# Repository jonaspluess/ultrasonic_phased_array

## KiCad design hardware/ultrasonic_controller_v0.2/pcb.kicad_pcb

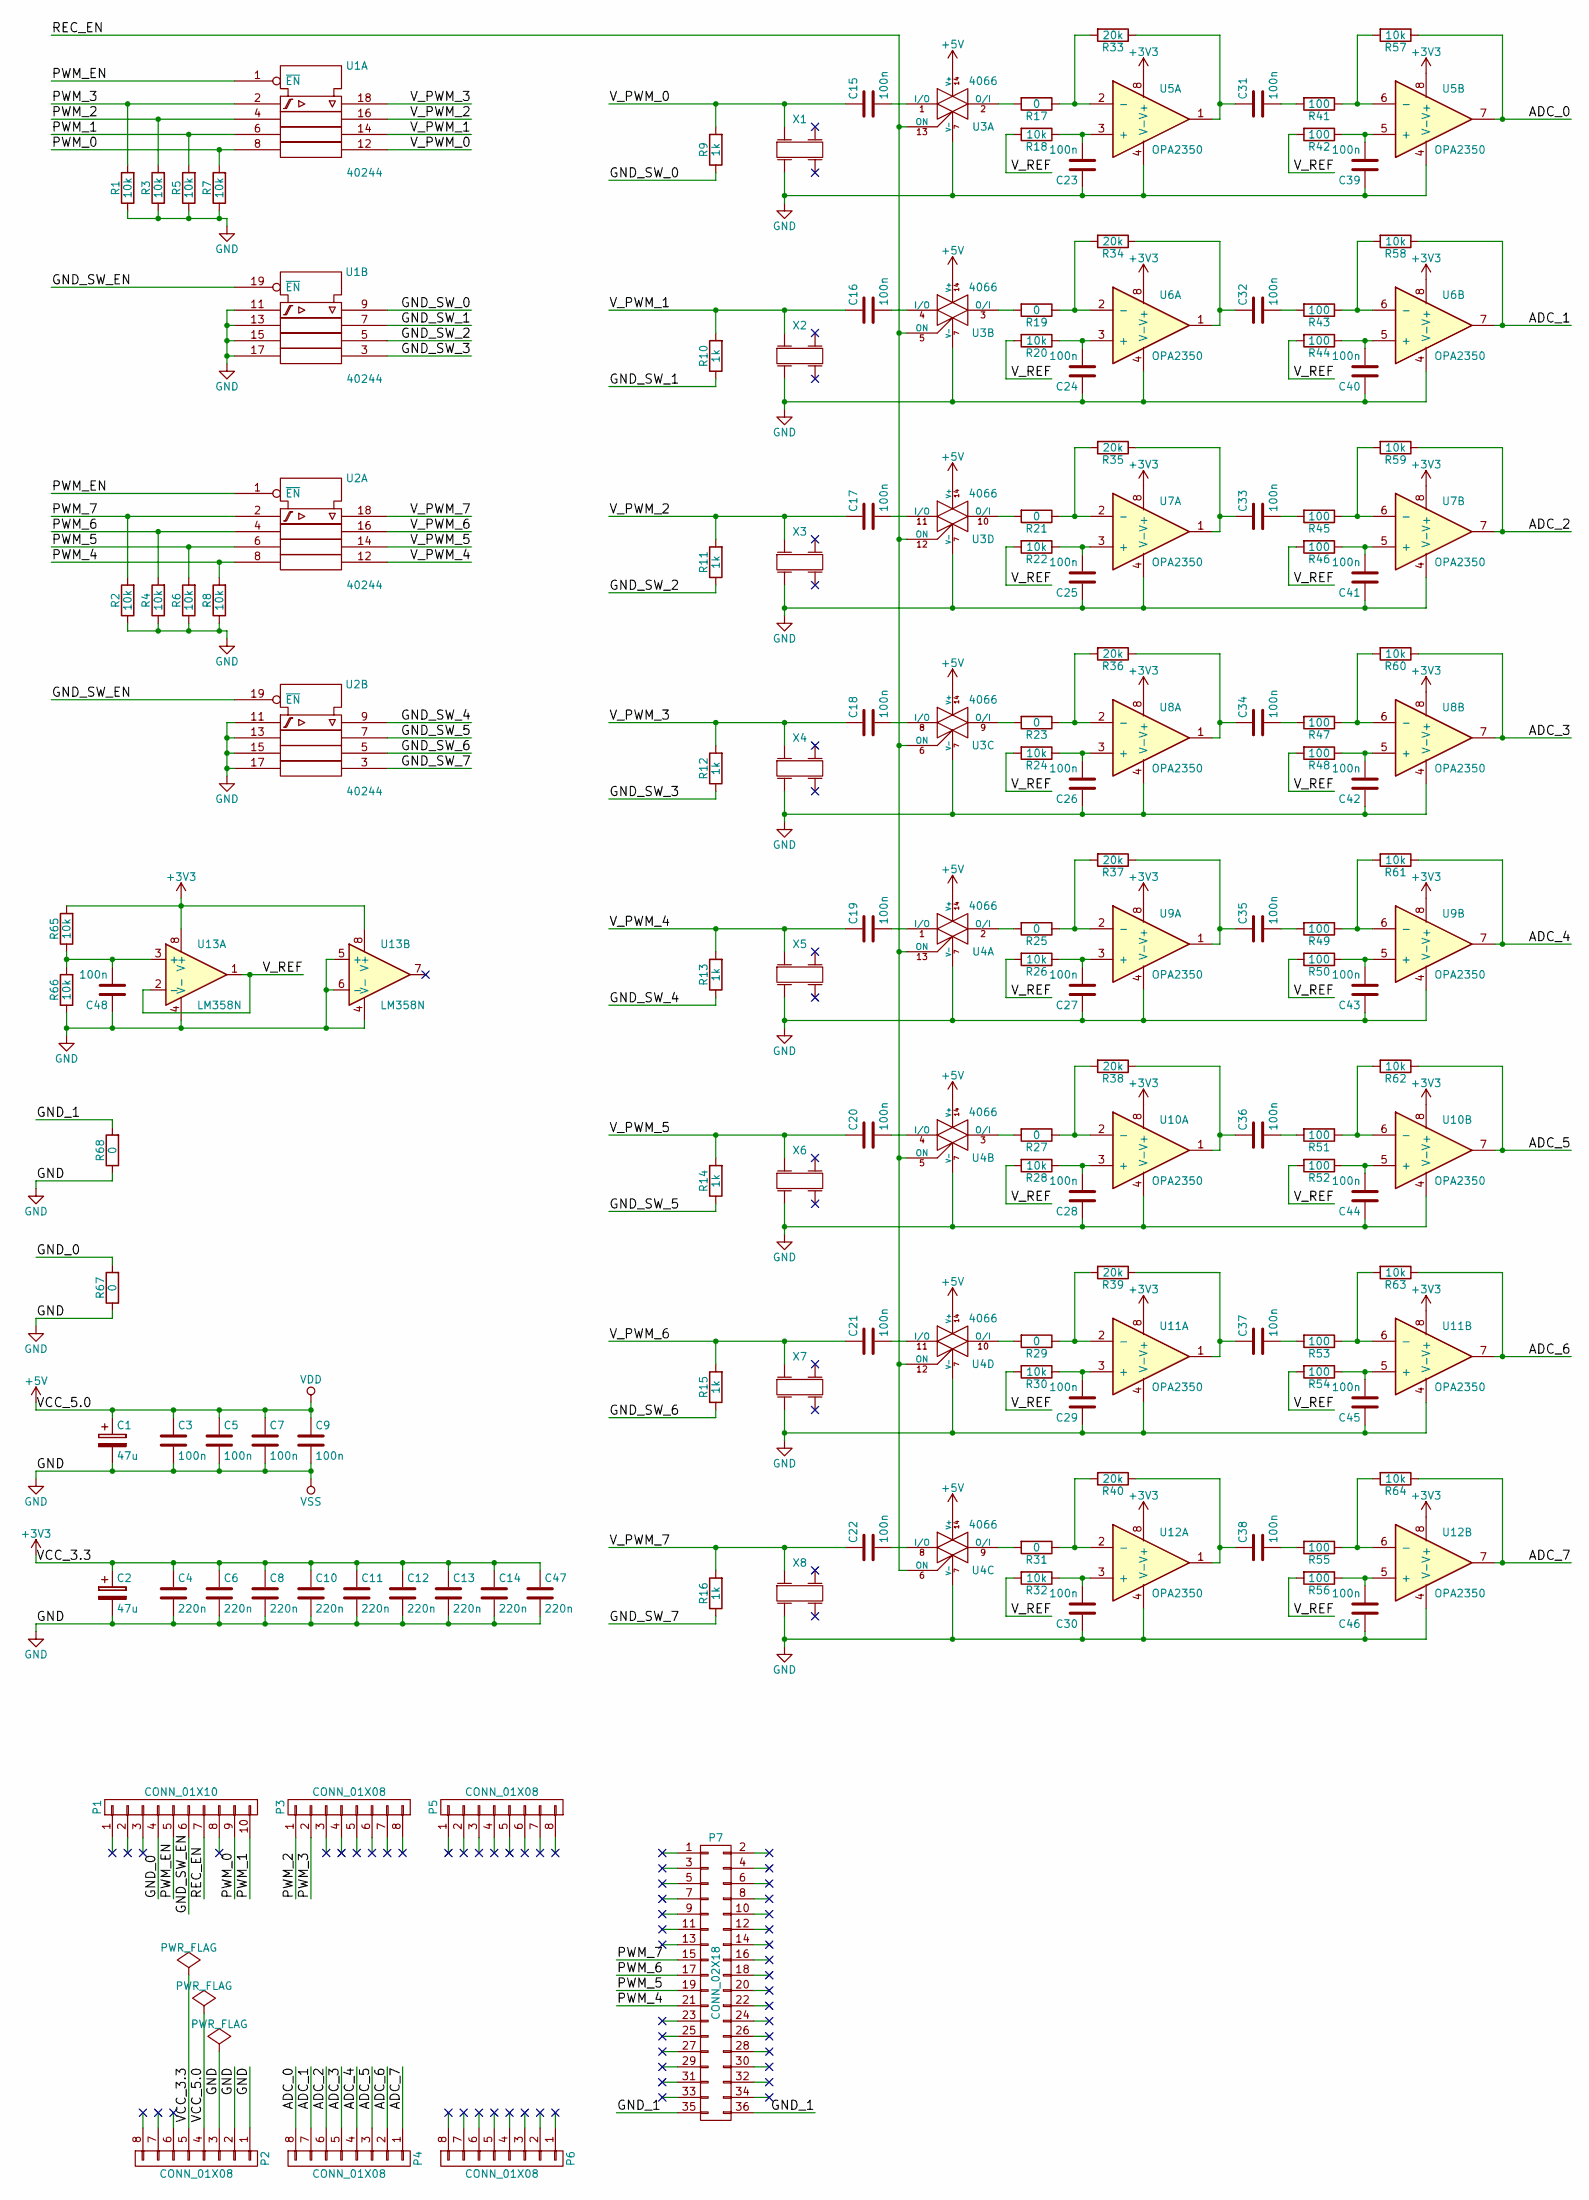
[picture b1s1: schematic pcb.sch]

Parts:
C1, C2: 47u; c_elec_6.3x5.8
C3, C5, C7, C9, C15, C16, C17, C18, C19, C20, C21, C22, C23, C24, C25, C26, C27, C28, C29, C30, C31, C32, C33, C34, C35, C36, C37, C38, C39, C40, C41, C42, C43, C44, C45, C46, C48: 100n; C_0805
C4, C6, C8, C10, C11, C12, C13, C14, C47: 220n; C_0805
P1: CONN_01X10; Pin_Header_Straight_1x10
P2, P3, P4, P5, P6: CONN_01X08; Pin_Header_Straight_1x08
P7: CONN_02X18; Pin_Header_Straight_2x18
R1, R2, R3, R4, R5, R6, R7, R8, R18, R20, R22, R24, R26, R28, R30, R32, R57, R58, R59, R60, R61, R62, R63, R64, R65, R66: 10k; R_0805
R9, R10, R11, R12, R13, R14, R15, R16: 1k; R_0805
R17, R19, R21, R23, R25, R27, R29, R31, R67, R68: 0; R_0805
R33, R34, R35, R36, R37, R38, R39, R40: 20k; R_0805
R41, R42, R43, R44, R45, R46, R47, R48, R49, R50, R51, R52, R53, R54, R55, R56: 100; R_0805
U1, U2: 40244; SOIC-20W_7.5x12.8mm_Pitch1.27mm
U3, U4: 4066; SOIC-14_N
U5, U6, U7, U8, U9, U10, U11, U12: OPA2350; SOIC-8_3.9x4.9mm_Pitch1.27mm
U13: LM358N; SOIC-8_3.9x4.9mm_Pitch1.27mm
X1, X2, X3, X4, X5, X6, X7, X8: PiezoelectricCrystal-TwoPairsOfelectrodes_EN60617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; murata_ultrasonic_transducer

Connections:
+3V3: C2.1, C4.1, C6.1, C8.1, C10.1, C11.1, C12.1, C13.1, C14.1, C47.1, P2.5, R65.2, U5.8 (V+), U6.8 (V+), U7.8 (V+), U8.8 (V+), U9.8 (V+), U10.8 (V+), U11.8 (V+), U12.8 (V+), U13.8 (V+)
+5V: C1.1, C3.1, C5.1, C7.1, C9.1, P2.4, U1.20 (Vdd), U2.20 (Vdd), U3.14 (V+), U4.14 (V+)
/ADC_0: P4.8, R57.1, U5.7
/ADC_1: P4.7, R58.1, U6.7
/ADC_2: P4.6, R59.1, U7.7
/ADC_3: P4.5, R60.1, U8.7
/ADC_4: P4.4, R61.1, U9.7
/ADC_5: P4.3, R62.1, U10.7
/ADC_6: P4.2, R63.1, U11.7
/ADC_7: P4.1, R64.1, U12.7
/GND_0: P1.4, R67.2
/GND_1: P7.35, P7.36, R68.2
/GND_SW_0: R9.1, U1.9
/GND_SW_1: R10.1, U1.7
/GND_SW_2: R11.1, U1.5
/GND_SW_3: R12.1, U1.3
/GND_SW_4: R13.1, U2.9
/GND_SW_5: R14.1, U2.7
/GND_SW_6: R15.1, U2.5
/GND_SW_7: R16.1, U2.3
/GND_SW_EN: P1.6, U1.19 (~EN), U2.19 (~EN)
/PWM_0: P1.9, R7.2, U1.8
/PWM_1: P1.10, R5.2, U1.6
/PWM_2: P3.1, R3.2, U1.4
/PWM_3: P3.2, R1.2, U1.2
/PWM_4: P7.21, R8.2, U2.8
/PWM_5: P7.19, R6.2, U2.6
/PWM_6: P7.17, R4.2, U2.4
/PWM_7: P7.15, R2.2, U2.2
/PWM_EN: P1.5, U1.1 (~EN), U2.1 (~EN)
/REC_EN: P1.7, U3.5 (ON), U3.6 (ON), U3.12 (ON), U3.13 (ON), U4.5 (ON), U4.6 (ON), U4.12 (ON), U4.13 (ON)
/V_PWM_0: C15.1, R9.2, U1.12, X1.1
/V_PWM_1: C16.1, R10.2, U1.14, X2.1
/V_PWM_2: C17.1, R11.2, U1.16, X3.1
/V_PWM_3: C18.1, R12.2, U1.18, X4.1
/V_PWM_4: C19.1, R13.2, U2.12, X5.1
/V_PWM_5: C20.1, R14.2, U2.14, X6.1
/V_PWM_6: C21.1, R15.2, U2.16, X7.1
/V_PWM_7: C22.1, R16.2, U2.18, X8.1
/V_REF: R18.2, R20.2, R22.2, R24.2, R26.2, R28.2, R30.2, R32.2, R42.2, R44.2, R46.2, R48.2, R50.2, R52.2, R54.2, R56.2, U13.1, U13.2 (-)
GND: C1.2, C2.2, C3.2, C4.2, C5.2, C6.2, C7.2, C8.2, C9.2, C10.2, C11.2, C12.2, C13.2, C14.2, C23.1, C24.1, C25.1, C26.1, C27.1, C28.1, C29.1, C30.1, C39.1, C40.1, C41.1, C42.1, C43.1, C44.1, C45.1, C46.1, C47.2, C48.1, P2.1, P2.2, P2.3, R1.1, R2.1, R3.1, R4.1, R5.1, R6.1, R7.1, R8.1, R66.1, R67.1, R68.1, U1.10 (Vss), U1.11, U1.13, U1.15, U1.17, U2.10 (Vss), U2.11, U2.13, U2.15, U2.17, U3.7 (V-), U4.7 (V-), U5.4 (V-), U6.4 (V-), U7.4 (V-), U8.4 (V-), U9.4 (V-), U10.4 (V-), U11.4 (V-), U12.4 (V-), U13.4 (V-), U13.5 (+), U13.6 (-), X1.3, X2.3, X3.3, X4.3, X5.3, X6.3, X7.3, X8.3
unnamed: C15.2, U3.1 (I/O)
unnamed: C16.2, U3.4 (I/O)
unnamed: C17.2, U3.11 (I/O)
unnamed: C18.2, U3.8 (I/O)
unnamed: C19.2, U4.1 (I/O)
unnamed: C20.2, U4.4 (I/O)
unnamed: C21.2, U4.11 (I/O)
unnamed: C22.2, U4.8 (I/O)
unnamed: C23.2, R18.1, U5.3 (+)
unnamed: C24.2, R20.1, U6.3 (+)
unnamed: C25.2, R22.1, U7.3 (+)
unnamed: C26.2, R24.1, U8.3 (+)
unnamed: C27.2, R26.1, U9.3 (+)
unnamed: C28.2, R28.1, U10.3 (+)
unnamed: C29.2, R30.1, U11.3 (+)
unnamed: C30.2, R32.1, U12.3 (+)
unnamed: C31.1, R33.1, U5.1
unnamed: C31.2, R41.2
unnamed: C32.1, R34.1, U6.1
unnamed: C32.2, R43.2
unnamed: C33.1, R35.1, U7.1
unnamed: C33.2, R45.2
unnamed: C34.1, R36.1, U8.1
unnamed: C34.2, R47.2
unnamed: C35.1, R37.1, U9.1
unnamed: C35.2, R49.2
unnamed: C36.1, R38.1, U10.1
unnamed: C36.2, R51.2
unnamed: C37.1, R39.1, U11.1
unnamed: C37.2, R53.2
unnamed: C38.1, R40.1, U12.1
unnamed: C38.2, R55.2
unnamed: C39.2, R42.1, U5.5 (+)
unnamed: C40.2, R44.1, U6.5 (+)
unnamed: C41.2, R46.1, U7.5 (+)
unnamed: C42.2, R48.1, U8.5 (+)
unnamed: C43.2, R50.1, U9.5 (+)
unnamed: C44.2, R52.1, U10.5 (+)
unnamed: C45.2, R54.1, U11.5 (+)
unnamed: C46.2, R56.1, U12.5 (+)
unnamed: C48.2, R65.1, R66.2, U13.3 (+)
unnamed: R17.1, R33.2, U5.2 (-)
unnamed: R17.2, U3.2 (O/I)
unnamed: R19.1, R34.2, U6.2 (-)
unnamed: R19.2, U3.3 (O/I)
unnamed: R21.1, R35.2, U7.2 (-)
unnamed: R21.2, U3.10 (O/I)
unnamed: R23.1, R36.2, U8.2 (-)
unnamed: R23.2, U3.9 (O/I)
unnamed: R25.1, R37.2, U9.2 (-)
unnamed: R25.2, U4.2 (O/I)
unnamed: R27.1, R38.2, U10.2 (-)
unnamed: R27.2, U4.3 (O/I)
unnamed: R29.1, R39.2, U11.2 (-)
unnamed: R29.2, U4.10 (O/I)
unnamed: R31.1, R40.2, U12.2 (-)
unnamed: R31.2, U4.9 (O/I)
unnamed: R41.1, R57.2, U5.6 (-)
unnamed: R43.1, R58.2, U6.6 (-)
unnamed: R45.1, R59.2, U7.6 (-)
unnamed: R47.1, R60.2, U8.6 (-)
unnamed: R49.1, R61.2, U9.6 (-)
unnamed: R51.1, R62.2, U10.6 (-)
unnamed: R53.1, R63.2, U11.6 (-)
unnamed: R55.1, R64.2, U12.6 (-)

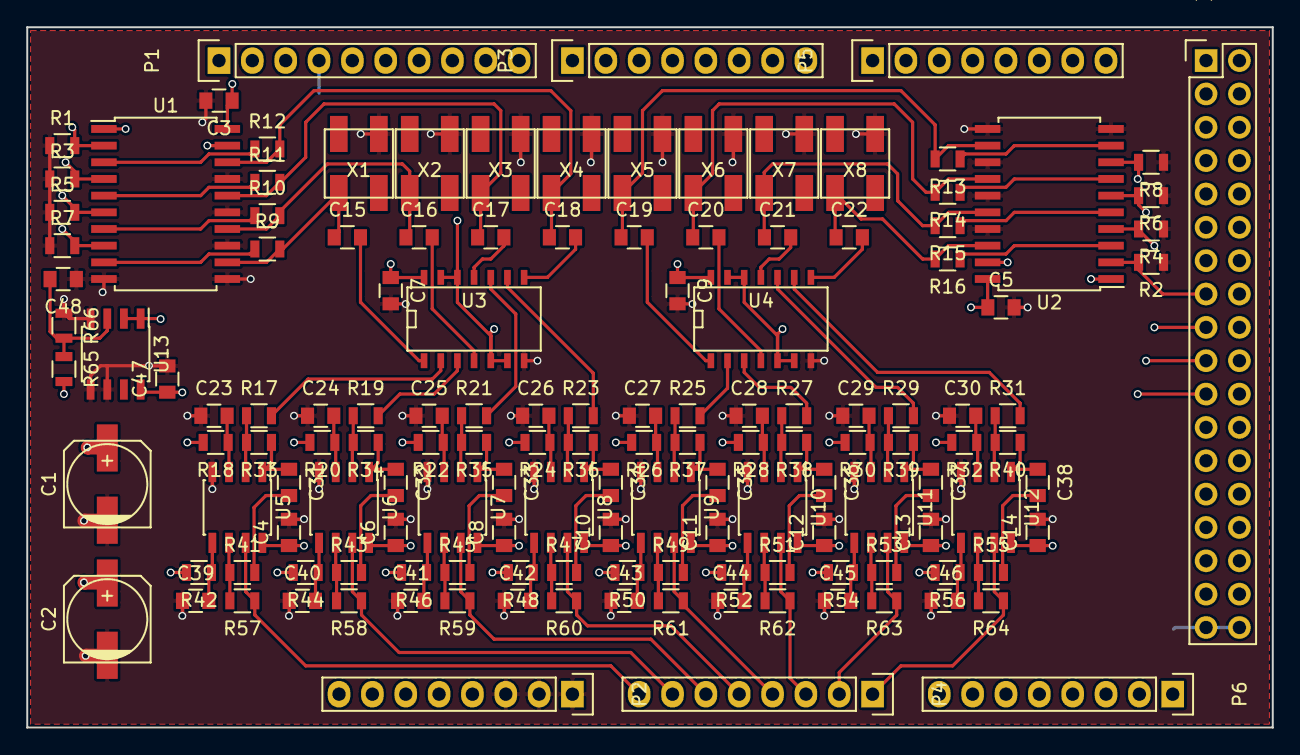
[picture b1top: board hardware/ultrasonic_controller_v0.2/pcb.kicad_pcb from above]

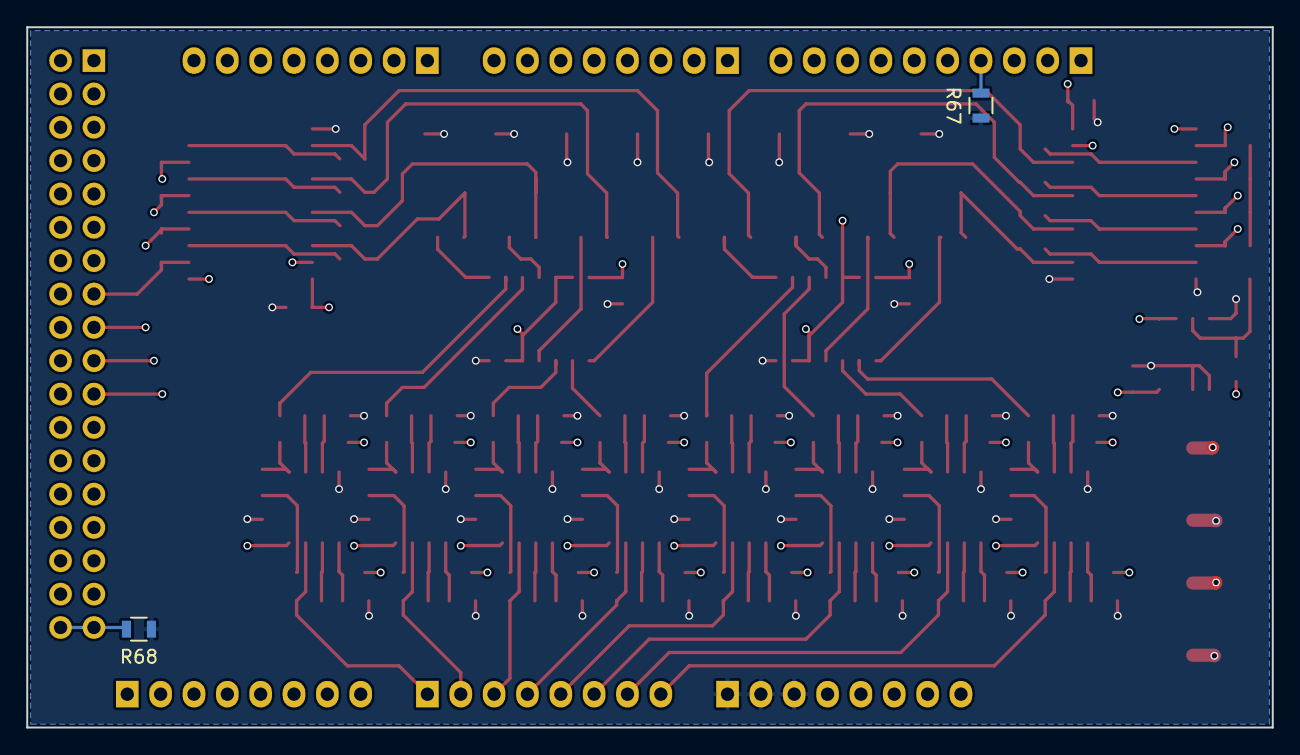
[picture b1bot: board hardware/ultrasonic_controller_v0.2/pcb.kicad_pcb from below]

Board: 4 copper layers, 94.9 x 53.3 mm, 144 parts (2 on the bottom side), 106 nets.

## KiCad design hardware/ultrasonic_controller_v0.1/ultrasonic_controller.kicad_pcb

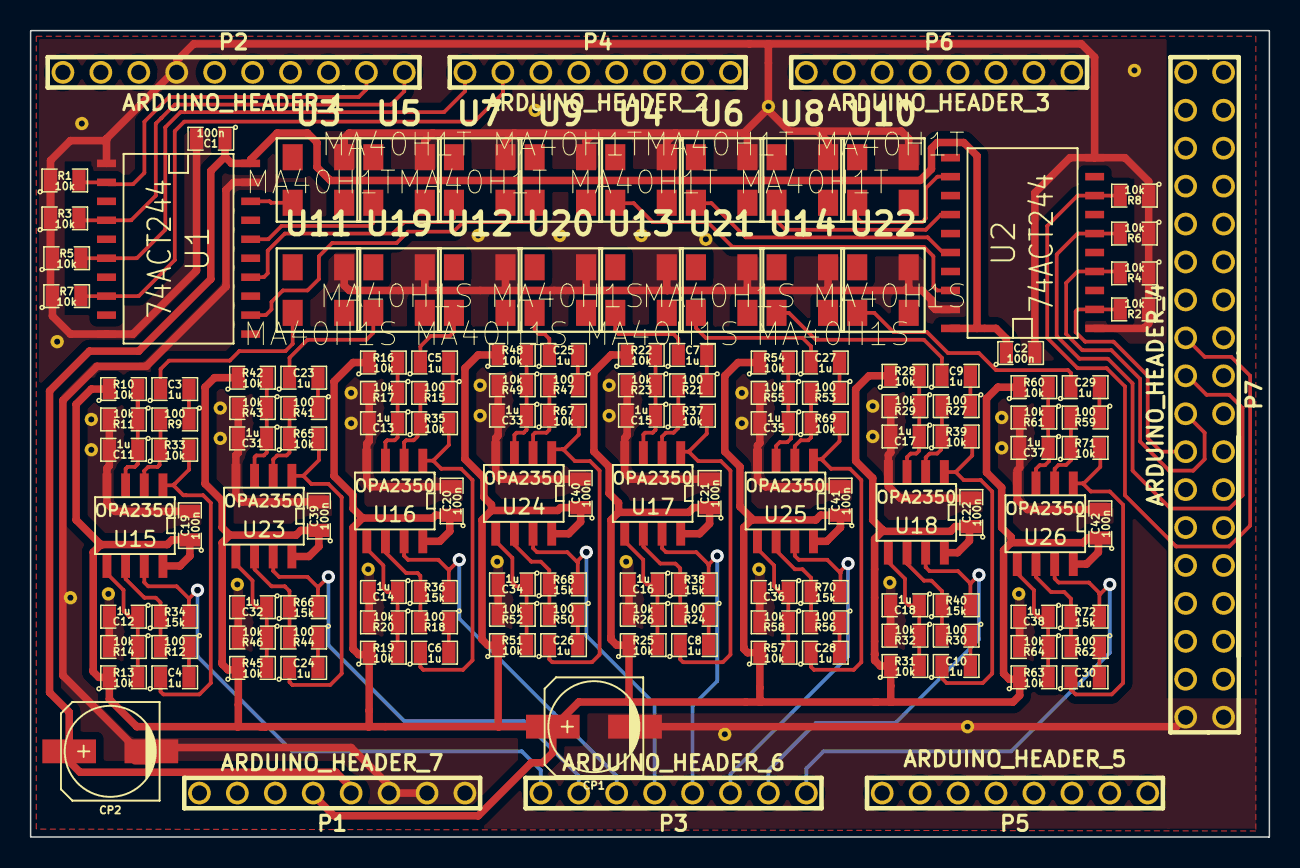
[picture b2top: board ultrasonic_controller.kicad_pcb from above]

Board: 2 copper layers, 82.9 x 54.0 mm, 188 parts (0 on the bottom side), 91 nets.

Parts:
C1, C2, C19, C20, C21, C22, C39, C40, C41, C42: 100n; SM0805
C3, C4, C5, C6, C7, C8, C9, C10, C11, C12, C13, C14, C15, C16, C17, C18, C23, C24, C25, C26, C27, C28, C29, C30, C31, C32, C33, C34, C35, C36, C37, C38: 1u; SM0805
CP1, CP2: 10u; c_elec_6.3x5.8
GroundVia: VAL**; GroundVia
GroundVia#2, GroundVia#3, GroundVia#4, GroundVia#5, GroundVia#6, GroundVia#7, GroundVia#8, GroundVia#9, GroundVia#10, GroundVia#11, GroundVia#12, GroundVia#13, GroundVia#14, GroundVia#15, GroundVia#16, GroundVia#17, GroundVia#18, GroundVia#19, GroundVia#20, GroundVia#21, GroundVia#22, GroundVia#23, GroundVia#24, GroundVia#25, GroundVia#26, GroundVia#27, GroundVia#28, GroundVia#29, GroundVia#30, GroundVia#31, GroundVia#32, GroundVia#33, GroundVia#34, GroundVia#35, GroundVia#36, GroundVia#37, GroundVia#38, GroundVia#39: VAL**; GroundVia
P1: ARDUINO_HEADER_7; pin_array_8x1
P2: ARDUINO_HEADER_1; pin_array_10x1
P3: ARDUINO_HEADER_6; pin_array_8x1
P4: ARDUINO_HEADER_2; pin_array_8x1
P5: ARDUINO_HEADER_5; pin_array_8x1
P6: ARDUINO_HEADER_3; pin_array_8x1
P7: ARDUINO_HEADER_4; pin_array_18x2
R1, R2, R3, R4, R5, R6, R7, R8, R10, R11, R13, R14, R16, R17, R19, R20, R22, R23, R25, R26, R28, R29, R31, R32, R33, R35, R37, R39, R42, R43, R45, R46, R48, R49, R51, R52, R54, R55, R57, R58, R60, R61, R63, R64, R65, R67, R69, R71: 10k; SM0805
R9, R12, R15, R18, R21, R24, R27, R30, R41, R44, R47, R50, R53, R56, R59, R62: 100; SM0805
R34, R36, R38, R40, R66, R68, R70, R72: 15k; SM0805
U1, U2: 74ACT244; SO20L
U3, U4, U5, U6, U7, U8, U9, U10: MA40H1T; 81-MA4OH1S
U11, U12, U13, U14, U19, U20, U21, U22: MA40H1S; 81-MA4OH1S
U15, U16, U17, U18, U23, U24, U25, U26: OPA2350; SOIC-8_N

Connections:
/5V: C1.1, C2.1, CP2.1, P1.4, U1.20, U2.20
/ADC_0: P3.8, R34.2, U15.7
/ADC_0_X: C4.1, R33.2, U15.1
/ADC_1: P3.7, R66.2, U23.7
/ADC_1_X: C24.1, R65.2, U23.1
/ADC_2: P3.6, R36.2, U16.7
/ADC_2_X: C6.1, R35.2, U16.1
/ADC_3: P3.5, R68.2, U24.7
/ADC_3_X: C26.1, R67.2, U24.1
/ADC_4: P3.4, R38.2, U17.7
/ADC_4_X: C8.1, R37.2, U17.1
/ADC_5: P3.3, R70.2, U25.7
/ADC_5_X: C28.1, R69.2, U25.1
/ADC_6: P3.2, R40.2, U18.7
/ADC_6_X: C10.1, R39.2, U18.1
/ADC_7: P3.1, R72.2, U26.7
/ADC_7_X: C30.1, R71.2, U26.1
/PWM_0: P2.9, R1.2, U1.2
/PWM_1: P2.10, R3.2, U1.4
/PWM_2: P4.1, R5.2, U1.6
/PWM_3: P4.2, R7.2, U1.8
/PWM_4: P7.21, R2.2, U2.2
/PWM_5: P7.19, R4.2, U2.4
/PWM_6: P7.17, R6.2, U2.6
/PWM_7: P7.15, R8.2, U2.8
/VCC: C19.1, C20.1, C21.1, C22.1, C39.1, C40.1, C41.1, C42.1, CP1.1, P1.5, R10.1, R13.1, R16.1, R19.1, R22.1, R25.1, R28.1, R31.1, R42.1, R45.1, R48.1, R51.1, R54.1, R57.1, R60.1, R63.1, U15.8, U16.8, U17.8, U18.8, U23.8, U24.8, U25.8, U26.8
GND: C1.2, C2.2, C11.2, C12.2, C13.2, C14.2, C15.2, C16.2, C17.2, C18.2, C19.2, C20.2, C21.2, C22.2, C31.2, C32.2, C33.2, C34.2, C35.2, C36.2, C37.2, C38.2, C39.2, C40.2, C41.2, C42.2, CP1.2, CP2.2, GroundVia.1, GroundVia#2.1, GroundVia#3.1, GroundVia#4.1, GroundVia#5.1, GroundVia#6.1, GroundVia#7.1, GroundVia#8.1, GroundVia#9.1, GroundVia#10.1, GroundVia#11.1, GroundVia#12.1, GroundVia#13.1, GroundVia#14.1, GroundVia#16.1, GroundVia#17.1, GroundVia#18.1, GroundVia#19.1, GroundVia#20.1, GroundVia#21.1, GroundVia#22.1, GroundVia#23.1, GroundVia#24.1, GroundVia#25.1, GroundVia#26.1, GroundVia#27.1, GroundVia#28.1, GroundVia#29.1, GroundVia#31.1, GroundVia#32.1, GroundVia#34.1, GroundVia#35.1, GroundVia#36.1, GroundVia#37.1, GroundVia#38.1, GroundVia#39.1, P1.1, P1.2, P1.3, P2.4, P7.35, P7.36, R1.1, R2.1, R3.1, R4.1, R5.1, R6.1, R7.1, R8.1, R11.2, R14.2, R17.2, R20.2, R23.2, R26.2, R29.2, R32.2, R43.2, R46.2, R49.2, R52.2, R55.2, R58.2, R61.2, R64.2, U1.1, U1.10, U1.19, U2.1, U2.10, U2.19, U3.3, U4.3, U5.3, U6.3, U7.3, U8.3, U9.3, U10.3, U11.3, U12.3, U13.3, U14.3, U15.4, U16.4, U17.4, U18.4, U19.3, U20.3, U21.3, U22.3, U23.4, U24.4, U25.4, U26.4
unnamed: C35.1, R54.2, R55.1, U25.3
unnamed: R56.2, R70.1, U25.6
unnamed: R53.2, R69.1, U25.2
unnamed: C36.1, R57.2, R58.1, U25.5
unnamed: C9.1, U14.1
unnamed: C10.2, R30.1
unnamed: C9.2, R27.1
unnamed: C27.1, U21.1
unnamed: R30.2, R40.1, U18.6
unnamed: C18.1, R31.2, R32.1, U18.5
unnamed: R27.2, R39.1, U18.2
unnamed: C17.1, R28.2, R29.1, U18.3
unnamed: C7.1, U13.1
unnamed: C8.2, R24.1
unnamed: C7.2, R21.1
unnamed: R24.2, R38.1, U17.6
unnamed: R47.2, R67.1, U24.2
unnamed: R50.2, R68.1, U24.6
unnamed: C34.1, R51.2, R52.1, U24.5
unnamed: C27.2, R53.1
unnamed: C16.1, R25.2, R26.1, U17.5
unnamed: R21.2, R37.1, U17.2
unnamed: C28.2, R56.1
unnamed: C15.1, R22.2, R23.1, U17.3
unnamed: U1.14, U7.1
unnamed: U1.12, U9.1
unnamed: U2.12, U10.1
unnamed: U2.14, U8.1
unnamed: U2.18, U4.1
unnamed: U2.16, U6.1
unnamed: R59.2, R71.1, U26.2
unnamed: R62.2, R72.1, U26.6
unnamed: C29.2, R59.1
unnamed: C30.2, R62.1
unnamed: C29.1, U22.1
unnamed: C37.1, R60.2, R61.1, U26.3
unnamed: U1.18, U3.1
unnamed: U1.16, U5.1
unnamed: C38.1, R63.2, R64.1, U26.5
unnamed: R12.2, R34.1, U15.6
unnamed: R9.2, R33.1, U15.2
unnamed: C12.1, R13.2, R14.1, U15.5
unnamed: C3.1, U11.1
unnamed: C11.1, R10.2, R11.1, U15.3
unnamed: C4.2, R12.1
unnamed: C3.2, R9.1
unnamed: C5.1, U12.1
unnamed: C6.2, R18.1
unnamed: C5.2, R15.1
unnamed: C32.1, R45.2, R46.1, U23.5
unnamed: C14.1, R19.2, R20.1, U16.5
unnamed: C25.1, U20.1
unnamed: C33.1, R48.2, R49.1, U24.3
unnamed: C26.2, R50.1
unnamed: R18.2, R36.1, U16.6
unnamed: R15.2, R35.1, U16.2
unnamed: C13.1, R16.2, R17.1, U16.3
unnamed: C25.2, R47.1
unnamed: R44.2, R66.1, U23.6
unnamed: R41.2, R65.1, U23.2
unnamed: C31.1, R42.2, R43.1, U23.3
unnamed: C24.2, R44.1
unnamed: C23.2, R41.1
unnamed: C23.1, U19.1

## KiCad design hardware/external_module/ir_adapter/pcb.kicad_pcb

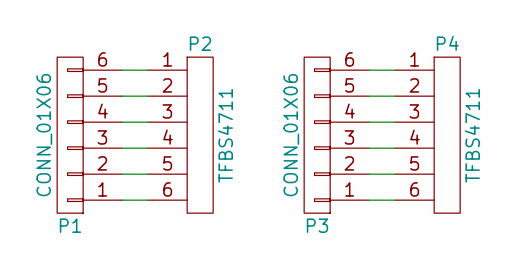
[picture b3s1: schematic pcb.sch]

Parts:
P1, P3: CONN_01X06; Pin_Header_Straight_1x06
P2, P4: TFBS4711

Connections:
unnamed: P1.1, P2.6
unnamed: P1.2, P2.5
unnamed: P1.3, P2.4
unnamed: P1.4, P2.3
unnamed: P1.5, P2.2
unnamed: P1.6, P2.1
unnamed: P3.1, P4.6
unnamed: P3.2, P4.5
unnamed: P3.3, P4.4
unnamed: P3.4, P4.3
unnamed: P3.5, P4.2
unnamed: P3.6, P4.1

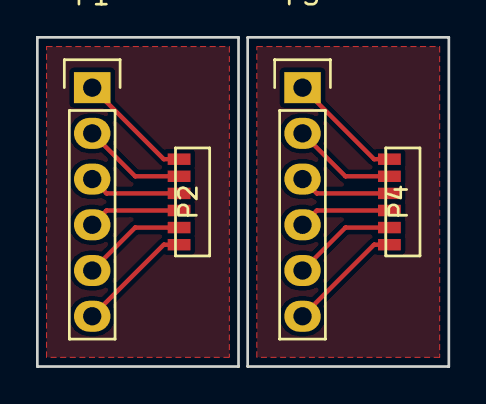
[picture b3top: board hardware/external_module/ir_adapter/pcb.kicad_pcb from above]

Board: 2 copper layers, 22.9 x 18.3 mm, 4 parts (0 on the bottom side), 12 nets.

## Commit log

2017-04-01 added .gitignore
2017-04-01 added twosided "fachbericht"
2017-05-26 added new plots.
